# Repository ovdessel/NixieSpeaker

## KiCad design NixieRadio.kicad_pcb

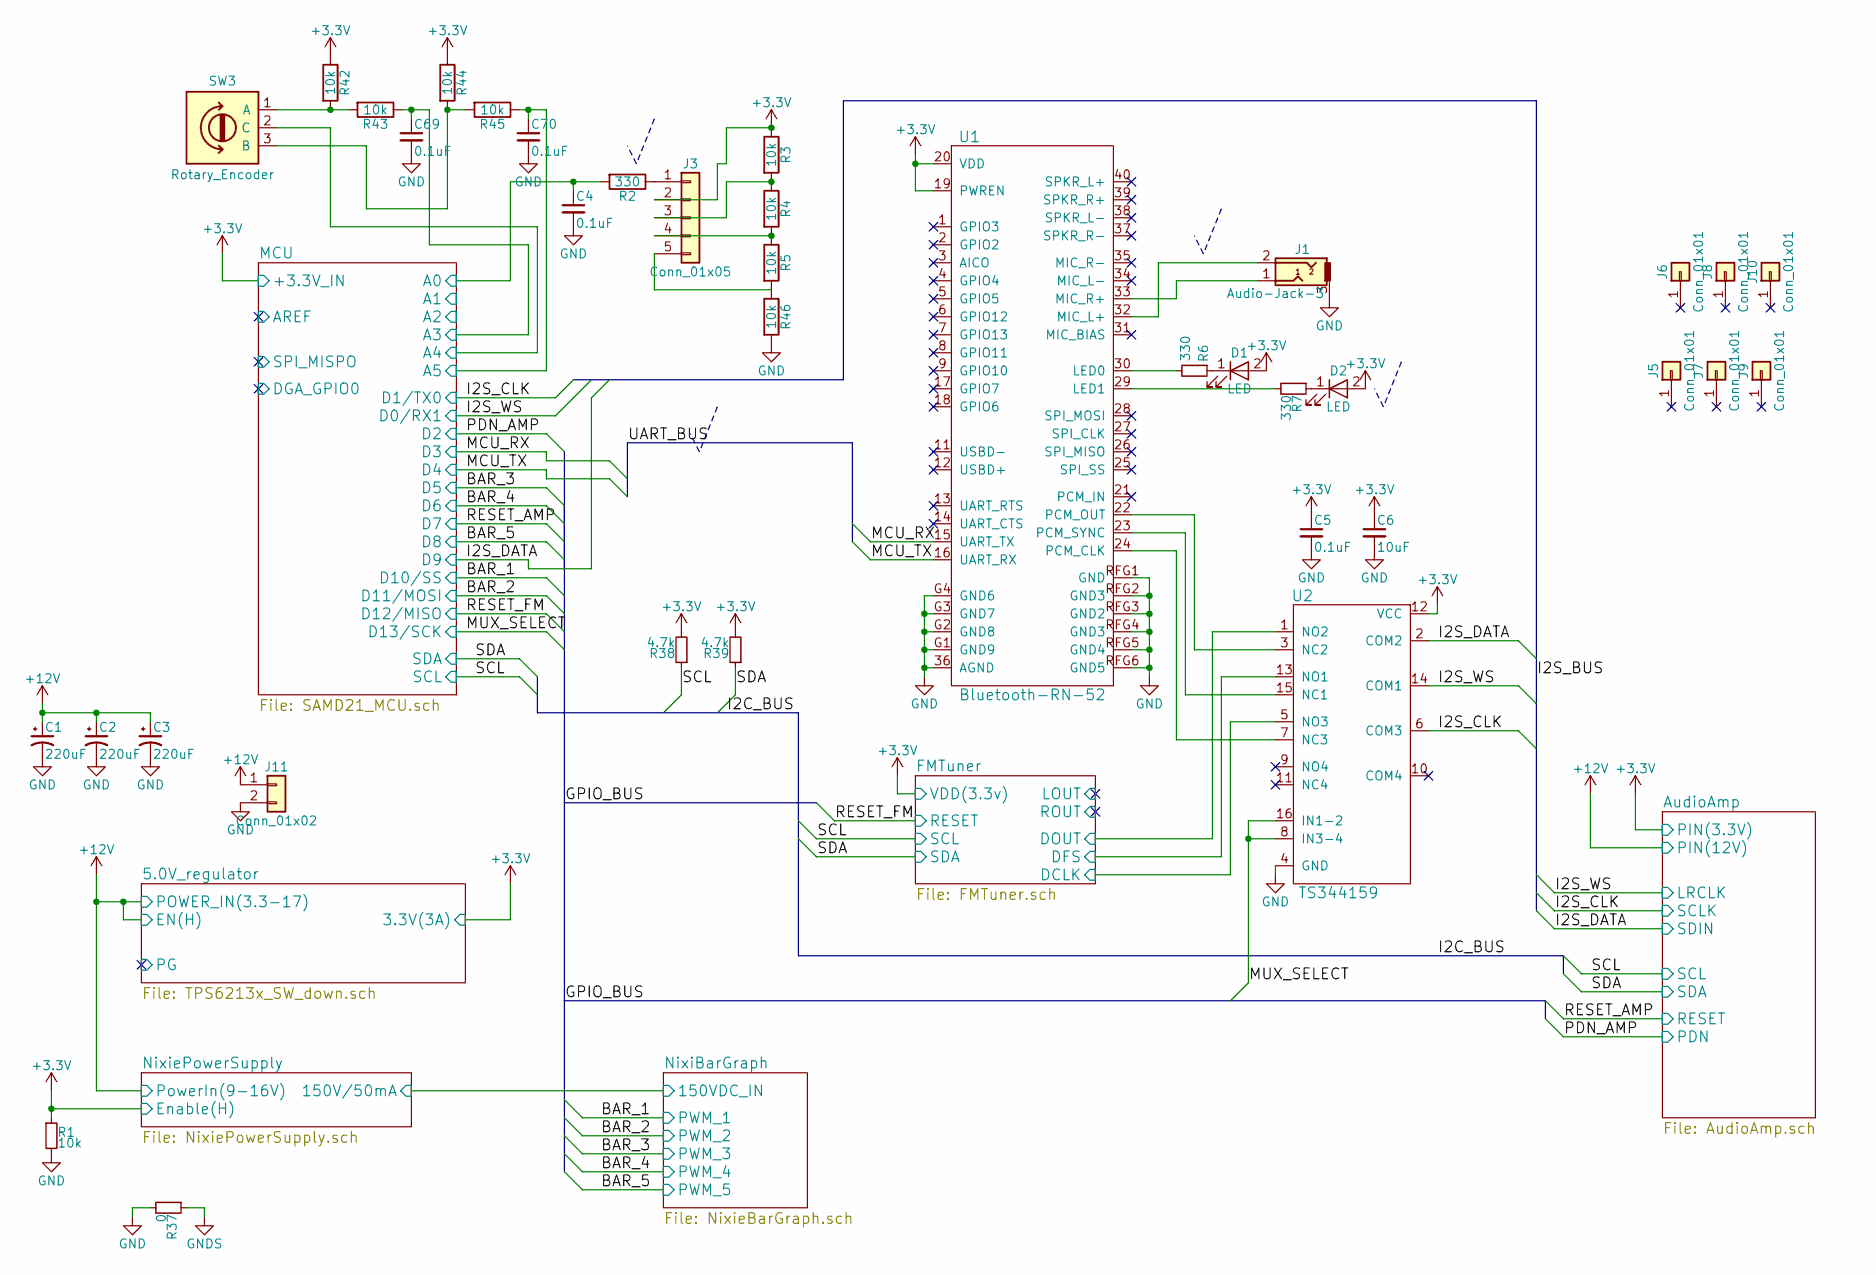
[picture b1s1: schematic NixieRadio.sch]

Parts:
C1, C2, C3: 220uF; CP_Elec_8x10
C4, C5, C69, C70: 0.1uF; 0603-CAP
C6: 10uF; 0603-CAP
D1, D2: LED; LED_0603
J1: Audio-Jack-3; 1X03
J3: Conn_01x05; 1X05
J5, J6, J7, J8, J9, J10: Conn_01x01; STAND-OFF
J11: Conn_01x02; 1X02_BIG
R1, R3, R4, R5, R42, R43, R44, R45, R46: 10k; 0603-RES
R2, R6, R7: 330; 0603-RES
R37: 0; R_1210_HandSoldering
R38, R39: 4.7k; 0603-RES
SW3: Rotary_Encoder; 1X03
U1: Bluetooth-RN-52; RN-52
U2: TS344159; TSSOP16

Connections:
+3V3: C5.1, C6.1, D1.2 (A), D2.2 (A), J3.2, R1.1, R3.1, R38.2, R39.2, R42.1, R44.1, U1.19 (PWREN), U1.20 (VDD), U2.12 (VCC); also elsewhere on the board
+12V: C1.1, C2.1, C3.1, J11.1; also elsewhere on the board
/FMTuner/DCLK: U2.5 (NO3); also elsewhere on the board
/FMTuner/DFS: U2.13 (NO1); also elsewhere on the board
/FMTuner/DOUT: U2.1 (NO2); also elsewhere on the board
/I2S_CLK: U2.6 (COM3); also elsewhere on the board
/I2S_DATA: U2.2 (COM2); also elsewhere on the board
/I2S_WS: U2.14 (COM1); also elsewhere on the board
/MCU/A0: C4.1, R2.2; also elsewhere on the board
/MCU/A3: C69.1, R43.1; also elsewhere on the board
/MCU/A4: SW3.2 (C); also elsewhere on the board
/MCU/A5: C70.1, R45.1; also elsewhere on the board
/MCU_RX: U1.15 (UART_TX); also elsewhere on the board
/MCU_TX: U1.16 (UART_RX); also elsewhere on the board
/MUX_SELECT: U2.8 (IN3-4), U2.16 (IN1-2); also elsewhere on the board
/SCL: R38.1; also elsewhere on the board
/SDA: R39.1; also elsewhere on the board
GND: C1.2, C2.2, C3.2, C4.2, C5.2, C6.2, C69.2, C70.2, J1.3, J11.2, R1.2, R37.2, R46.2, U1.36 (AGND), U1.G1 (GND9), U1.G2 (GND8), U1.G3 (GND7), U1.G4 (GND6), U1.RFG1 (GND), U1.RFG2 (GND3), U1.RFG3 (GND2), U1.RFG4 (GND3), U1.RFG5 (GND4), U1.RFG6 (GND5), U2.4 (GND); also elsewhere on the board
GNDS: R37.1; also elsewhere on the board
unnamed: D1.1 (K), R6.1
unnamed: D2.1 (K), R7.1
unnamed: J1.1, U1.33 (MIC_R+)
unnamed: J1.2, U1.32 (MIC_L+)
unnamed: J3.1, R2.1
unnamed: J3.3, R3.2, R4.1
unnamed: J3.4, R4.2, R5.1
unnamed: J3.5, R5.2, R46.1
unnamed: R6.2, U1.30 (LED0)
unnamed: R7.2, U1.29 (LED1)
unnamed: R42.2, R43.2, SW3.1 (A)
unnamed: R44.2, R45.2, SW3.3 (B)
unnamed: U1.22 (PCM_OUT), U2.3 (NC2)
unnamed: U1.23 (PCM_SYNC), U2.15 (NC1)
unnamed: U1.24 (PCM_CLK), U2.7 (NC3)

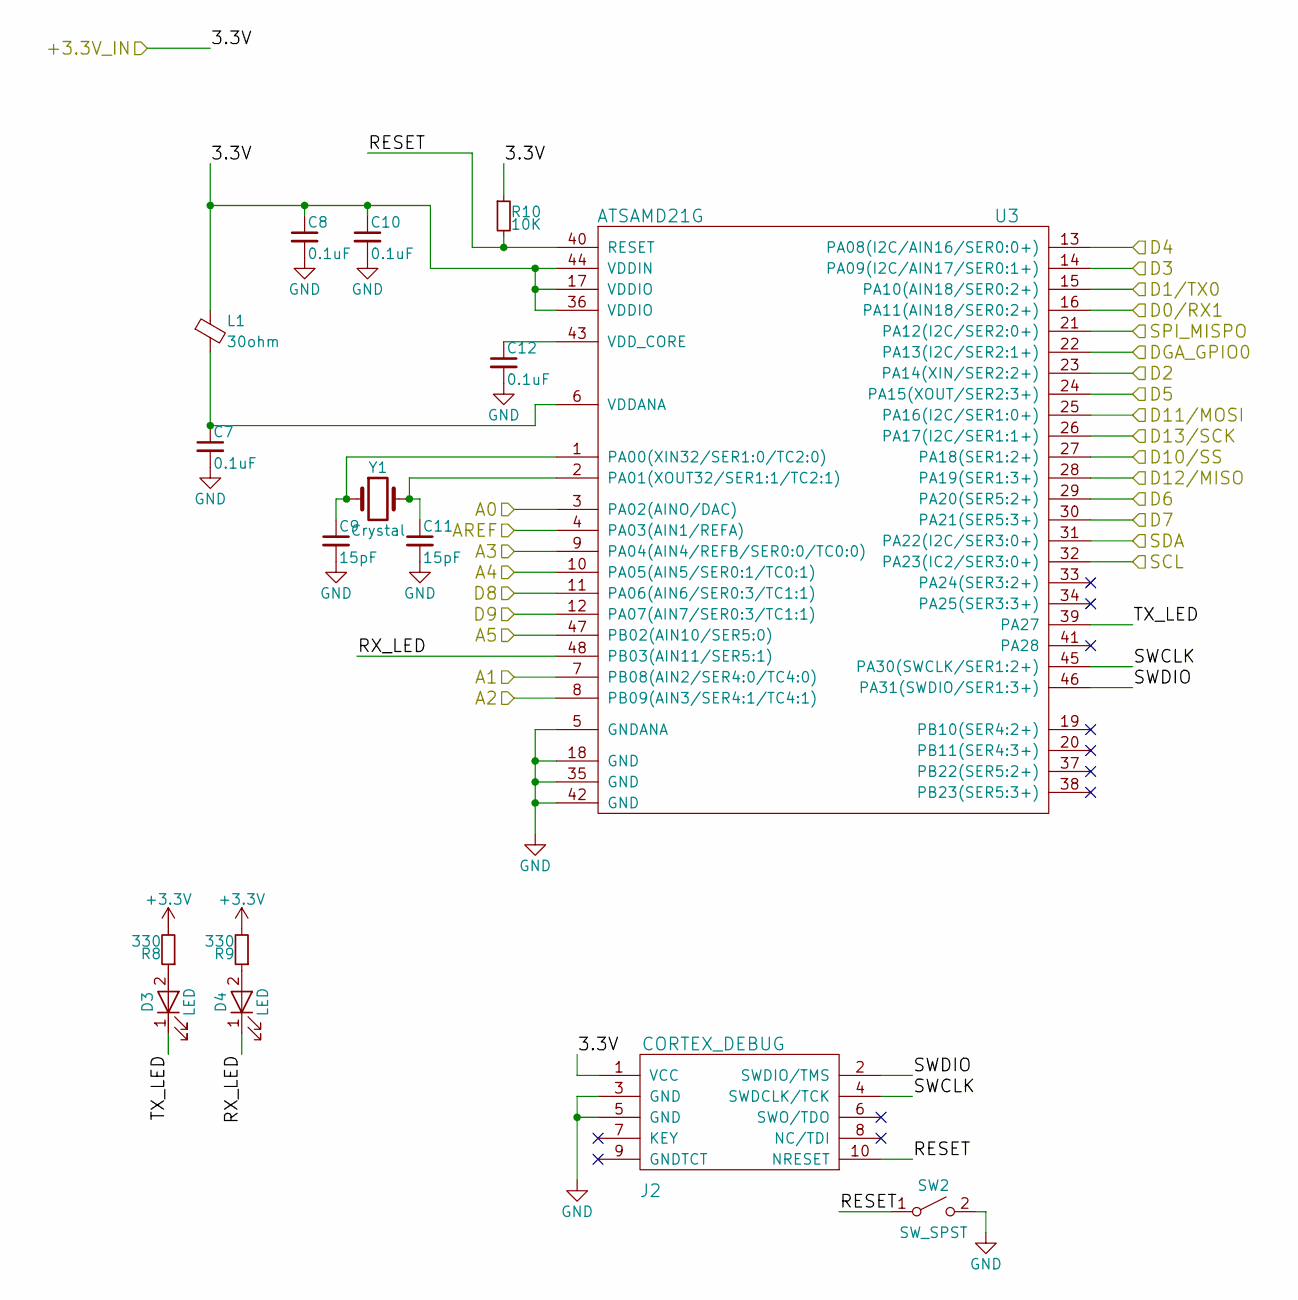
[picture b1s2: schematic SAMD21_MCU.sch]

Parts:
C7, C8, C10, C12: 0.1uF; 0603-CAP
C9, C11: 15pF; 0603-CAP
D3, D4: LED; LED_0603
J2: CORTEX_DEBUG; 2X5-PTH-1.27MM
L1: 30ohm; R_0603
R8, R9: 330; 0603-RES
R10: 10K; 0603-RES
SW2: SW_SPST; SW_SPST_B3U-1000P
U3: ATSAMD21G; TQFP-48
Y1: Crystal; Crystal_AT310_d3.0mm_l10.0mm_Horizontal

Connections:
+3V3: C8.1, C10.1, J2.1 (VCC), L1.1, R8.2, R9.2, R10.1, U3.17 (VDDIO), U3.36 (VDDIO), U3.44 (VDDIN); also elsewhere on the board
/BAR_1: U3.27 (PA18(SER1:2+)); also elsewhere on the board
/BAR_2: U3.25 (PA16(I2C/SER1:0+)); also elsewhere on the board
/BAR_3: U3.24 (PA15(XOUT/SER2:3+)); also elsewhere on the board
/BAR_4: U3.29 (PA20(SER5:2+)); also elsewhere on the board
/BAR_5: U3.11 (PA06(AIN6/SER0:3/TC1:1)); also elsewhere on the board
/I2S_CLK: U3.15 (PA10(AIN18/SER0:2+)); also elsewhere on the board
/I2S_DATA: U3.12 (PA07(AIN7/SER0:3/TC1:1)); also elsewhere on the board
/I2S_WS: U3.16 (PA11(AIN18/SER0:2+)); also elsewhere on the board
/MCU/A0: U3.3 (PA02(AINO/DAC)); also elsewhere on the board
/MCU/A1: U3.7 (PB08(AIN2/SER4:0/TC4:0))
/MCU/A2: U3.8 (PB09(AIN3/SER4:1/TC4:1))
/MCU/A3: U3.9 (PA04(AIN4/REFB/SER0:0/TC0:0)); also elsewhere on the board
/MCU/A4: U3.10 (PA05(AIN5/SER0:1/TC0:1)); also elsewhere on the board
/MCU/A5: U3.47 (PB02(AIN10/SER5:0)); also elsewhere on the board
/MCU/AREF: U3.4 (PA03(AIN1/REFA))
/MCU/DGA_GPIO0: U3.22 (PA13(I2C/SER2:1+))
/MCU/RESET: J2.10 (NRESET), R10.2, SW2.1 (A), U3.40 (RESET)
/MCU/RX_LED: D4.1 (K), U3.48 (PB03(AIN11/SER5:1))
/MCU/SPI_MISPO: U3.21 (PA12(I2C/SER2:0+))
/MCU/SWCLK: J2.4 (SWDCLK/TCK), U3.45 (PA30(SWCLK/SER1:2+))
/MCU/SWDIO: J2.2 (SWDIO/TMS), U3.46 (PA31(SWDIO/SER1:3+))
/MCU/TX_LED: D3.1 (K), U3.39 (PA27)
/MCU_RX: U3.14 (PA09(I2C/AIN17/SER0:1+)); also elsewhere on the board
/MCU_TX: U3.13 (PA08(I2C/AIN16/SER0:0+)); also elsewhere on the board
/MUX_SELECT: U3.26 (PA17(I2C/SER1:1+)); also elsewhere on the board
/PDN_AMP: U3.23 (PA14(XIN/SER2:2+)); also elsewhere on the board
/RESET_AMP: U3.30 (PA21(SER5:3+)); also elsewhere on the board
/RESET_FM: U3.28 (PA19(SER1:3+)); also elsewhere on the board
/SCL: U3.32 (PA23(IC2/SER3:0+)); also elsewhere on the board
/SDA: U3.31 (PA22(I2C/SER3:0+)); also elsewhere on the board
GND: C7.2, C8.2, C9.2, C10.2, C11.2, C12.2, J2.3 (GND), J2.5 (GND), SW2.2 (B), U3.5 (GNDANA), U3.18 (GND), U3.35 (GND), U3.42 (GND); also elsewhere on the board
unnamed: C7.1, L1.2, U3.6 (VDDANA)
unnamed: C9.1, U3.1 (PA00(XIN32/SER1:0/TC2:0)), Y1.1
unnamed: C11.1, U3.2 (PA01(XOUT32/SER1:1/TC2:1)), Y1.2
unnamed: C12.1, U3.43 (VDD_CORE)
unnamed: D3.2 (A), R8.1
unnamed: D4.2 (A), R9.1

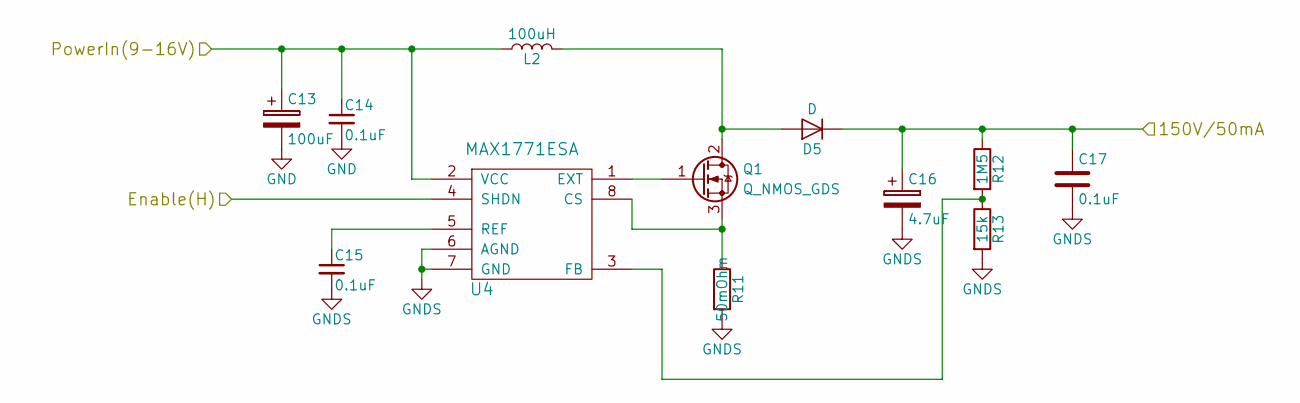
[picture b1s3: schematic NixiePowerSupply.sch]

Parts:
C13: 100uF; CP_Elec_8x10
C14, C15: 0.1uF; 0603-CAP
C16: 4.7uF; CP_Elec_10x10
C17: 0.1uF; C_2225_HandSoldering
D5: D; D_SMB
L2: 100uH; Inductor_Taiyo-Yuden_NR-80xx_HandSoldering
Q1: Q_NMOS_GDS; TO-220-3_Horizontal_Reversed
R11: 50mOhm; R_1210_HandSoldering
R12: 1M5; R_1210_HandSoldering
R13: 15k; 0603-RES
U4: MAX1771ESA; SO08

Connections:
+3V3: U4.4 (SHDN); also elsewhere on the board
+12V: C13.1, C14.1, L2.1, U4.2 (VCC); also elsewhere on the board
/NixiePowerSupply/150V/50mA: C16.1, C17.1, D5.1 (K), R12.1; also elsewhere on the board
GND: C13.2, C14.2; also elsewhere on the board
GNDS: C15.2, C16.2, C17.2, R11.2, R13.2, U4.6 (AGND), U4.7 (GND); also elsewhere on the board
unnamed: C15.1, U4.5 (REF)
unnamed: D5.2 (A), L2.2, Q1.2 (D)
unnamed: Q1.1 (G), U4.1 (EXT)
unnamed: Q1.3 (S), R11.1, U4.8 (CS)
unnamed: R12.2, R13.1, U4.3 (FB)

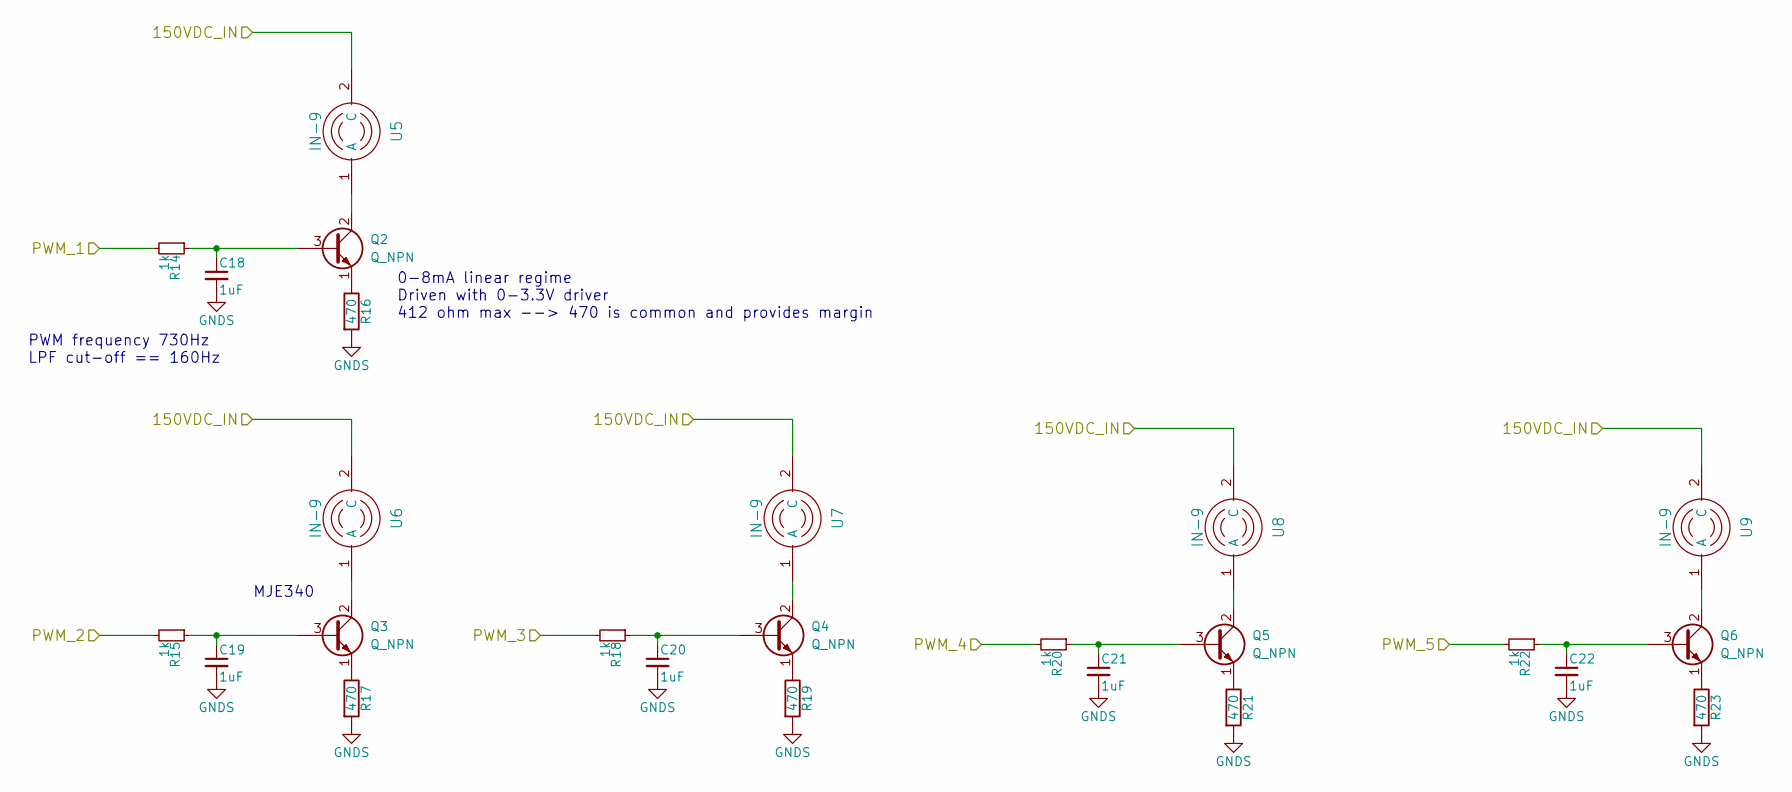
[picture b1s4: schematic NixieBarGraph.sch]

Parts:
C18, C19, C20, C21, C22: 1uF; 0603-CAP
Q2, Q3, Q4, Q5, Q6: Q_NPN; TO-92
R14, R15, R18, R20, R22: 1k; 0603-RES
R16, R17, R19, R21, R23: 470; 0603-RES
U5, U6, U7, U8, U9: IN-9; 1X02

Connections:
/BAR_1: R14.2; also elsewhere on the board
/BAR_2: R15.2; also elsewhere on the board
/BAR_3: R18.2; also elsewhere on the board
/BAR_4: R20.2; also elsewhere on the board
/BAR_5: R22.2; also elsewhere on the board
/NixiePowerSupply/150V/50mA: U5.2 (C), U6.2 (C), U7.2 (C), U8.2 (C), U9.2 (C); also elsewhere on the board
GNDS: C18.2, C19.2, C20.2, C21.2, C22.2, R16.2, R17.2, R19.2, R21.2, R23.2; also elsewhere on the board
unnamed: C18.1, Q2.3 (B), R14.1
unnamed: C19.1, Q3.3 (B), R15.1
unnamed: C20.1, Q4.3 (B), R18.1
unnamed: C21.1, Q5.3 (B), R20.1
unnamed: C22.1, Q6.3 (B), R22.1
unnamed: Q2.1 (E), R16.1
unnamed: Q2.2 (C), U5.1 (A)
unnamed: Q3.1 (E), R17.1
unnamed: Q3.2 (C), U6.1 (A)
unnamed: Q4.1 (E), R19.1
unnamed: Q4.2 (C), U7.1 (A)
unnamed: Q5.1 (E), R21.1
unnamed: Q5.2 (C), U8.1 (A)
unnamed: Q6.1 (E), R23.1
unnamed: Q6.2 (C), U9.1 (A)

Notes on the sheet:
0-8mA linear regime Driven with 0-3.3V driver 412 ohm max --> 470 is common and provides margin
PWM frequency 730Hz LPF cut-off == 160Hz
MJE340

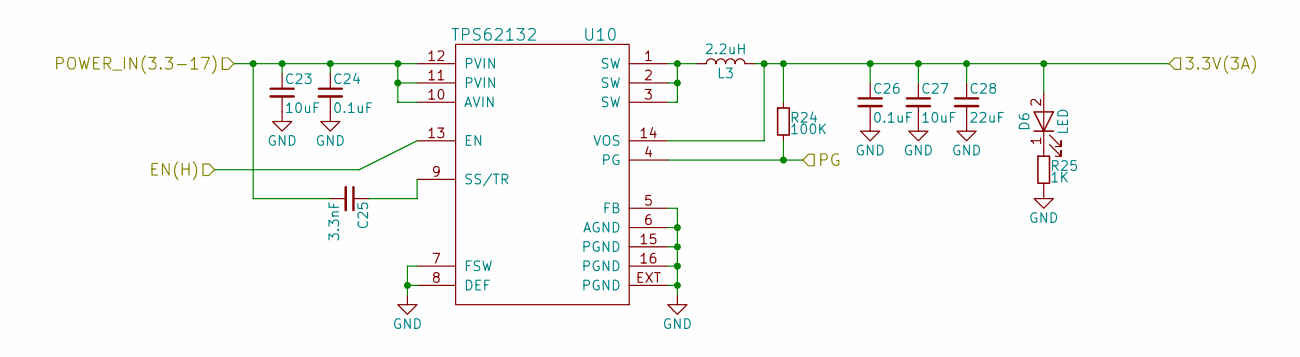
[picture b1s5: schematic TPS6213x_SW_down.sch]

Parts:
C23, C27: 10uF; 0603-CAP
C24, C26: 0.1uF; 0603-CAP
C25: 3.3nF; 0603-CAP
C28: 22uF; 0603-CAP
D6: LED; LED_0603
L3: 2.2uH; Inductor_1212
R24: 100K; 0603-RES
R25: 1K; 0603-RES
U10: TPS62132; QFN16-3X3MM_1%3a1_V03

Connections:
+3V3: C26.1, C27.1, C28.1, D6.2 (A), L3.2, R24.1, U10.14 (VOS); also elsewhere on the board
+12V: C23.1, C24.1, C25.2, U10.10 (AVIN), U10.11 (PVIN), U10.12 (PVIN), U10.13 (EN); also elsewhere on the board
/5.0V_regulator/PG: R24.2, U10.4 (PG)
GND: C23.2, C24.2, C26.2, C27.2, C28.2, R25.2, U10.5 (FB), U10.6 (AGND), U10.7 (FSW), U10.8 (DEF), U10.15 (PGND), U10.16 (PGND), U10.EXT (PGND); also elsewhere on the board
unnamed: C25.1, U10.9 (SS/TR)
unnamed: D6.1 (K), R25.1
unnamed: L3.1, U10.1 (SW), U10.2 (SW), U10.3 (SW)

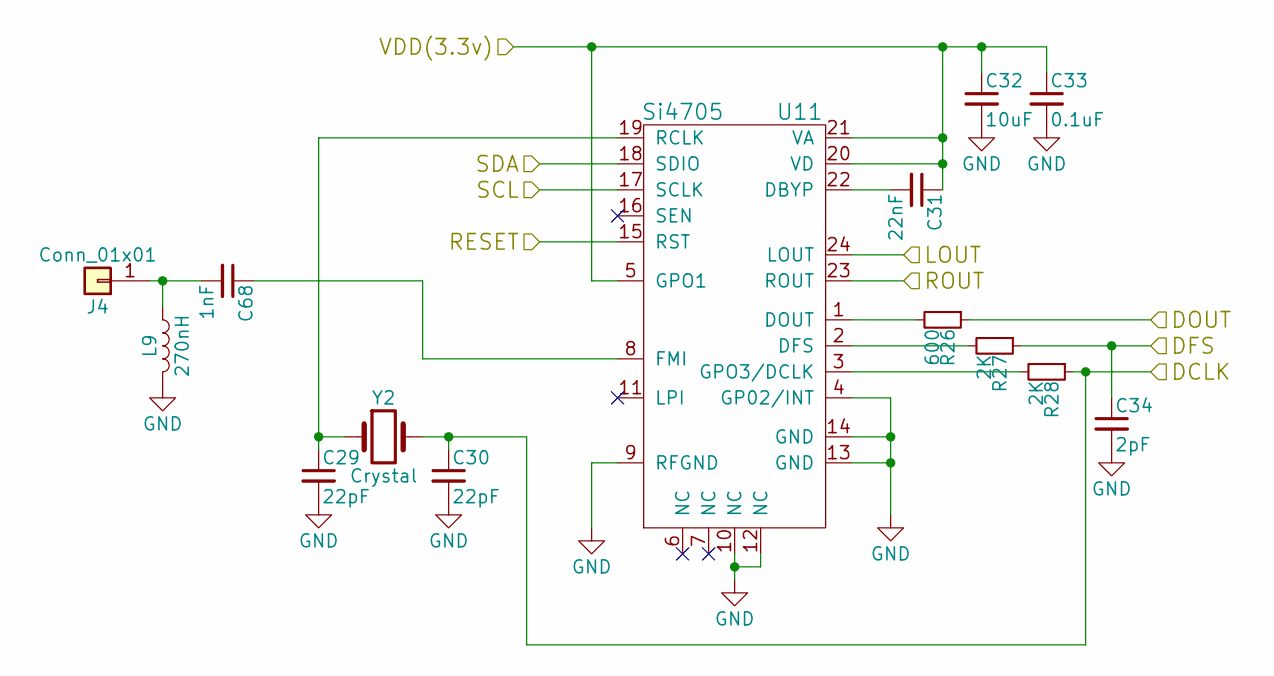
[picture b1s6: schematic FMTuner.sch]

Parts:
C29, C30: 22pF; 0603-CAP
C31: 22nF; 0603-CAP
C32: 10uF; 0603-CAP
C33: 0.1uF; 0603-CAP
C34: 2pF; 0603-CAP
C68: 1nF; 0603-CAP
J4: Conn_01x01; 1X01
L9: 270nH; Inductor_1212
R26: 600; 0603-RES
R27, R28: 2K; 0603-RES
U11: Si4705; SSOP24
Y2: Crystal; Crystal_AT310_d3.0mm_l10.0mm_Horizontal

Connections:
+3V3: C31.1, C32.1, C33.1, U11.5 (GPO1), U11.20 (VD), U11.21 (VA); also elsewhere on the board
/FMTuner/DCLK: C30.1, R28.1, Y2.2; also elsewhere on the board
/FMTuner/DFS: C34.1, R27.1; also elsewhere on the board
/FMTuner/DOUT: R26.1; also elsewhere on the board
/FMTuner/LOUT: U11.24 (LOUT)
/FMTuner/ROUT: U11.23 (ROUT)
/RESET_FM: U11.15 (RST); also elsewhere on the board
/SCL: U11.17 (SCLK); also elsewhere on the board
/SDA: U11.18 (SDIO); also elsewhere on the board
GND: C29.2, C30.2, C32.2, C33.2, C34.2, L9.2, U11.4 (GP02/INT), U11.9 (RFGND), U11.10 (NC), U11.12 (NC), U11.13 (GND), U11.14 (GND); also elsewhere on the board
unnamed: C29.1, U11.19 (RCLK), Y2.1
unnamed: C31.2, U11.22 (DBYP)
unnamed: C68.1, U11.8 (FMI)
unnamed: C68.2, J4.1, L9.1
unnamed: R26.2, U11.1 (DOUT)
unnamed: R27.2, U11.2 (DFS)
unnamed: R28.2, U11.3 (GPO3/DCLK)

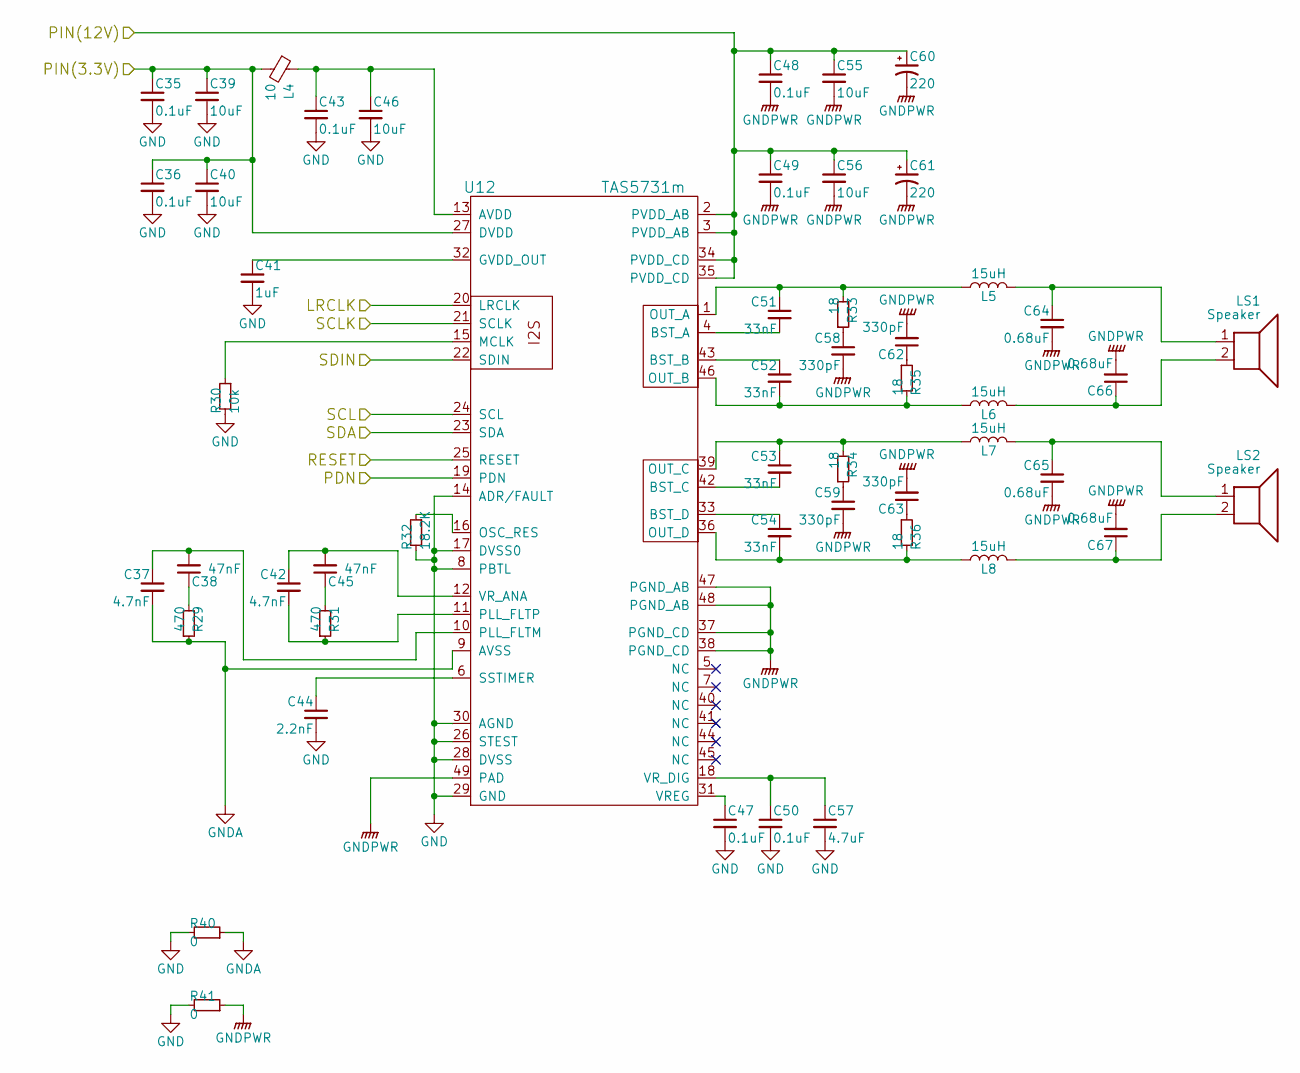
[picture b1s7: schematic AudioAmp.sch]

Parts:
C35, C36, C43, C47, C48, C49, C50: 0.1uF; 0603-CAP
C37, C42: 4.7nF; 0603-CAP
C38, C45: 47nF; 0603-CAP
C39, C40, C46, C55, C56: 10uF; 0603-CAP
C41: 1uF; 0603-CAP
C44: 2.2nF; 0603-CAP
C51, C52, C53, C54: 33nF; 0603-CAP
C57: 4.7uF; 0603-CAP
C58, C59, C62, C63: 330pF; 0603-CAP
C60, C61: 220; CP_Elec_8x10
C64, C65, C66, C67: 0.68uF; 0603-CAP
L4: 10; R_0603
L5, L6, L7, L8: 15uH; Inductor_Taiyo-Yuden_NR-60xx_HandSoldering
LS1, LS2: Speaker; GTK2400-V2
R29, R31: 470; 0603-RES
R30: 10k; 0603-RES
R32: 18.2K; 0603-RES
R33, R34, R35, R36: 18; 0603-RES
R40, R41: 0; R_1210_HandSoldering
U12: TAS5731m

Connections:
+3V3: C35.1, C36.1, C39.1, C40.1, L4.2, U12.27 (DVDD); also elsewhere on the board
+12V: C48.1, C49.1, C55.1, C56.1, C60.1, C61.1, U12.2 (PVDD_AB), U12.3 (PVDD_AB), U12.34 (PVDD_CD), U12.35 (PVDD_CD); also elsewhere on the board
/I2S_CLK: U12.21 (SCLK); also elsewhere on the board
/I2S_DATA: U12.22 (SDIN); also elsewhere on the board
/I2S_WS: U12.20 (LRCLK); also elsewhere on the board
/PDN_AMP: U12.19 (PDN); also elsewhere on the board
/RESET_AMP: U12.25 (RESET); also elsewhere on the board
/SCL: U12.24 (SCL); also elsewhere on the board
/SDA: U12.23 (SDA); also elsewhere on the board
GND: C35.2, C36.2, C39.2, C40.2, C41.2, C43.2, C44.2, C46.2, C47.2, C50.2, C57.2, R30.2, R32.2, R40.2, R41.2, U12.8 (PBTL), U12.14 (ADR/FAULT), U12.17 (DVSS0), U12.26 (STEST), U12.28 (DVSS), U12.29 (GND), U12.30 (AGND); also elsewhere on the board
GNDA: C37.2, R29.1, R40.1, U12.9 (AVSS)
GNDPWR: C48.2, C49.2, C55.2, C56.2, C58.2, C59.2, C60.2, C61.2, C62.2, C63.2, C64.2, C65.2, C66.2, C67.2, R41.1, U12.37 (PGND_CD), U12.38 (PGND_CD), U12.47 (PGND_AB), U12.48 (PGND_AB), U12.49 (PAD)
unnamed: C37.1, C38.2, U12.10 (PLL_FLTM)
unnamed: C38.1, R29.2
unnamed: C41.1, U12.32 (GVDD_OUT)
unnamed: C42.1, C45.2, U12.12 (VR_ANA)
unnamed: C42.2, R31.1, U12.11 (PLL_FLTP)
unnamed: C43.1, C46.1, L4.1, U12.13 (AVDD)
unnamed: C44.1, U12.6 (SSTIMER)
unnamed: C45.1, R31.2
unnamed: C47.1, U12.31 (VREG)
unnamed: C50.1, C57.1, U12.18 (VR_DIG)
unnamed: C51.1, L5.1, R33.2, U12.1 (OUT_A)
unnamed: C51.2, U12.4 (BST_A)
unnamed: C52.1, U12.43 (BST_B)
unnamed: C52.2, L6.1, R35.2, U12.46 (OUT_B)
unnamed: C53.1, L7.1, R34.2, U12.39 (OUT_C)
unnamed: C53.2, U12.42 (BST_C)
unnamed: C54.1, U12.33 (BST_D)
unnamed: C54.2, L8.1, R36.2, U12.36 (OUT_D)
unnamed: C58.1, R33.1
unnamed: C59.1, R34.1
unnamed: C62.1, R35.1
unnamed: C63.1, R36.1
unnamed: C64.1, L5.2, LS1.1
unnamed: C65.1, L7.2, LS2.1
unnamed: C66.1, L6.2, LS1.2
unnamed: C67.1, L8.2, LS2.2
unnamed: R30.1, U12.15 (MCLK)
unnamed: R32.1, U12.16 (OSC_RES)

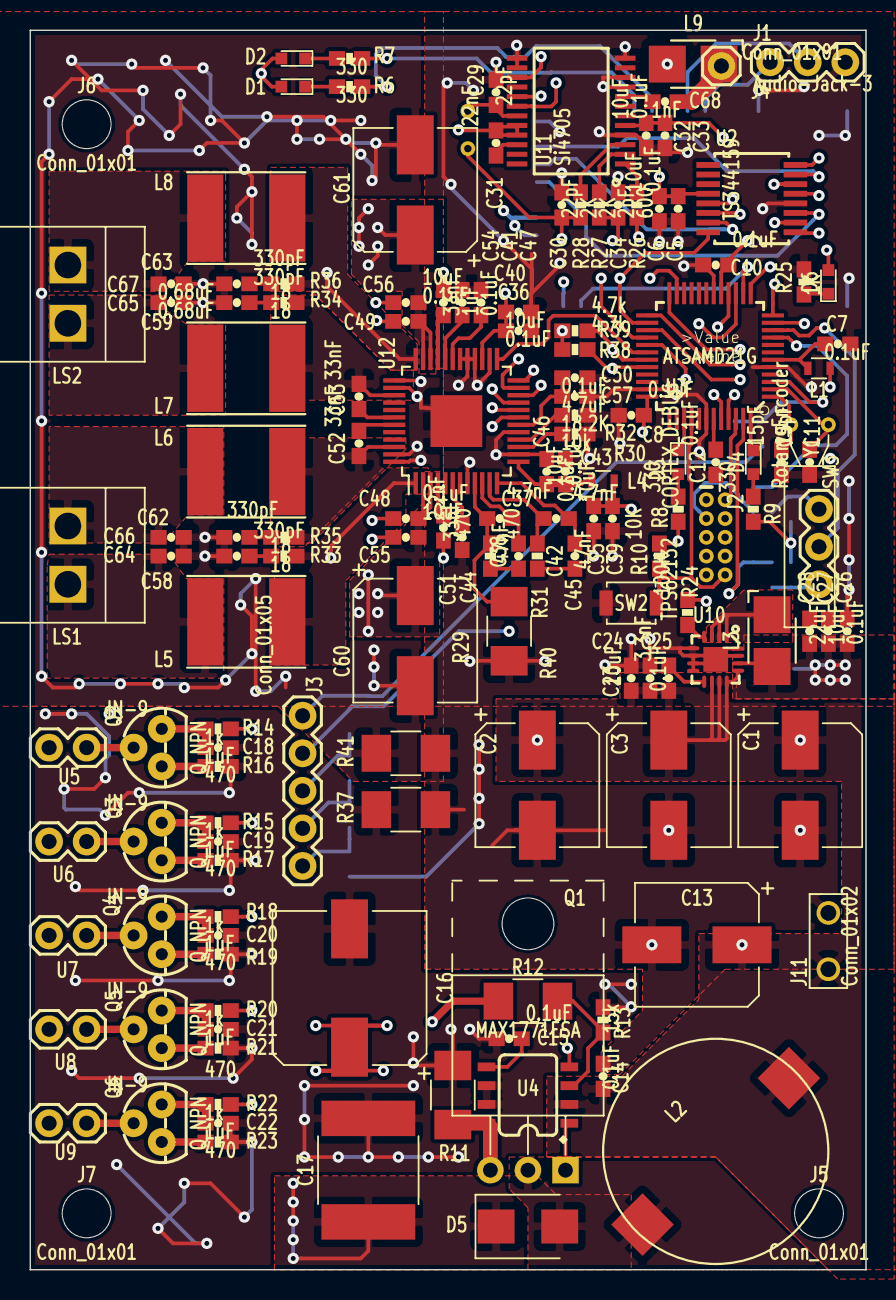
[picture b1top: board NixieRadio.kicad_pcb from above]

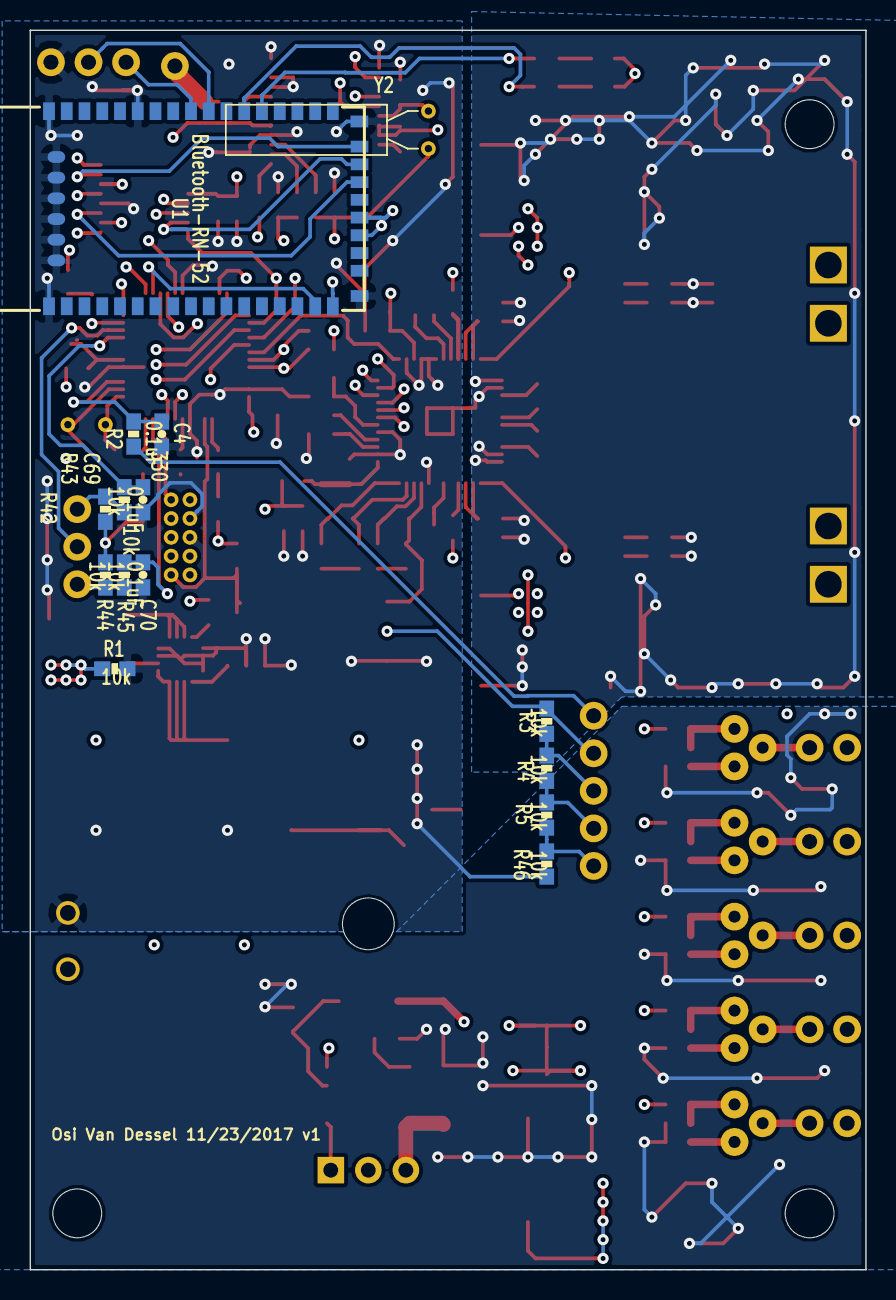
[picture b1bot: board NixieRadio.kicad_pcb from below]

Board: 4 copper layers, 56.5 x 83.8 mm, 163 parts (15 on the bottom side), 115 nets.
